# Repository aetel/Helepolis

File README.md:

Helepolis is an **educative** robot for those who want to have their **first contact** with robotics.

It's based around the Arduino platform, using an Arduino Nano as its brain.
It can be programmed to complete numerous tasks such as line following and sumo fighting.

---
### The machine includes:
* An Arduino Nano with ATMega 328p
* SHARP Distance Sensor
* 5 Reflective IR Sensors
* Differential Traction with 2 Pololu Micromotors
* Bluetooth module.
* 2 WS2812 RGB LED
* 4 5mm led
* I2C or SPI Expansion Module Port (intended use is for an ADXL345 3-axis accelerometer)
* Buzzer
* A few switches for general use

---
### In this repository you will find:
* EagleCAD project
<br>&nbsp;&nbsp;Includes the schematic and the PCB files
* TestCode
<br>&nbsp;&nbsp;A program to check all the sensors and actuators are working fine
* ExampleCode
<br>&nbsp;&nbsp;Line follower and sumo bot example program
* Assembly manuals
<br>&nbsp;&nbsp;Guided assembly manuals in English and Spanish
* BoM
<br>&nbsp;&nbsp;Bill of Materials used for the robot

---
### Android app:
You can download the app to control the robot at [Google Play](https://play.google.com/store/apps/details?id=aetel.helepolis), though you may be interested in building or modifying the code available in this repository.

---

Helepolis and its surrounding materials are published under [CC BY-SA 4.0](https://creativecommons.org/licenses/by-sa/4.0/)

Helepolis was designed by [Pablo dMM](https://github.com/PabloDMM "Pablo dMM") for Telecom Electronics Association [AETEL](http://aetel.io), based at the Campus Sur of [Universidad Politécnica de Madrid](http://upm.es).

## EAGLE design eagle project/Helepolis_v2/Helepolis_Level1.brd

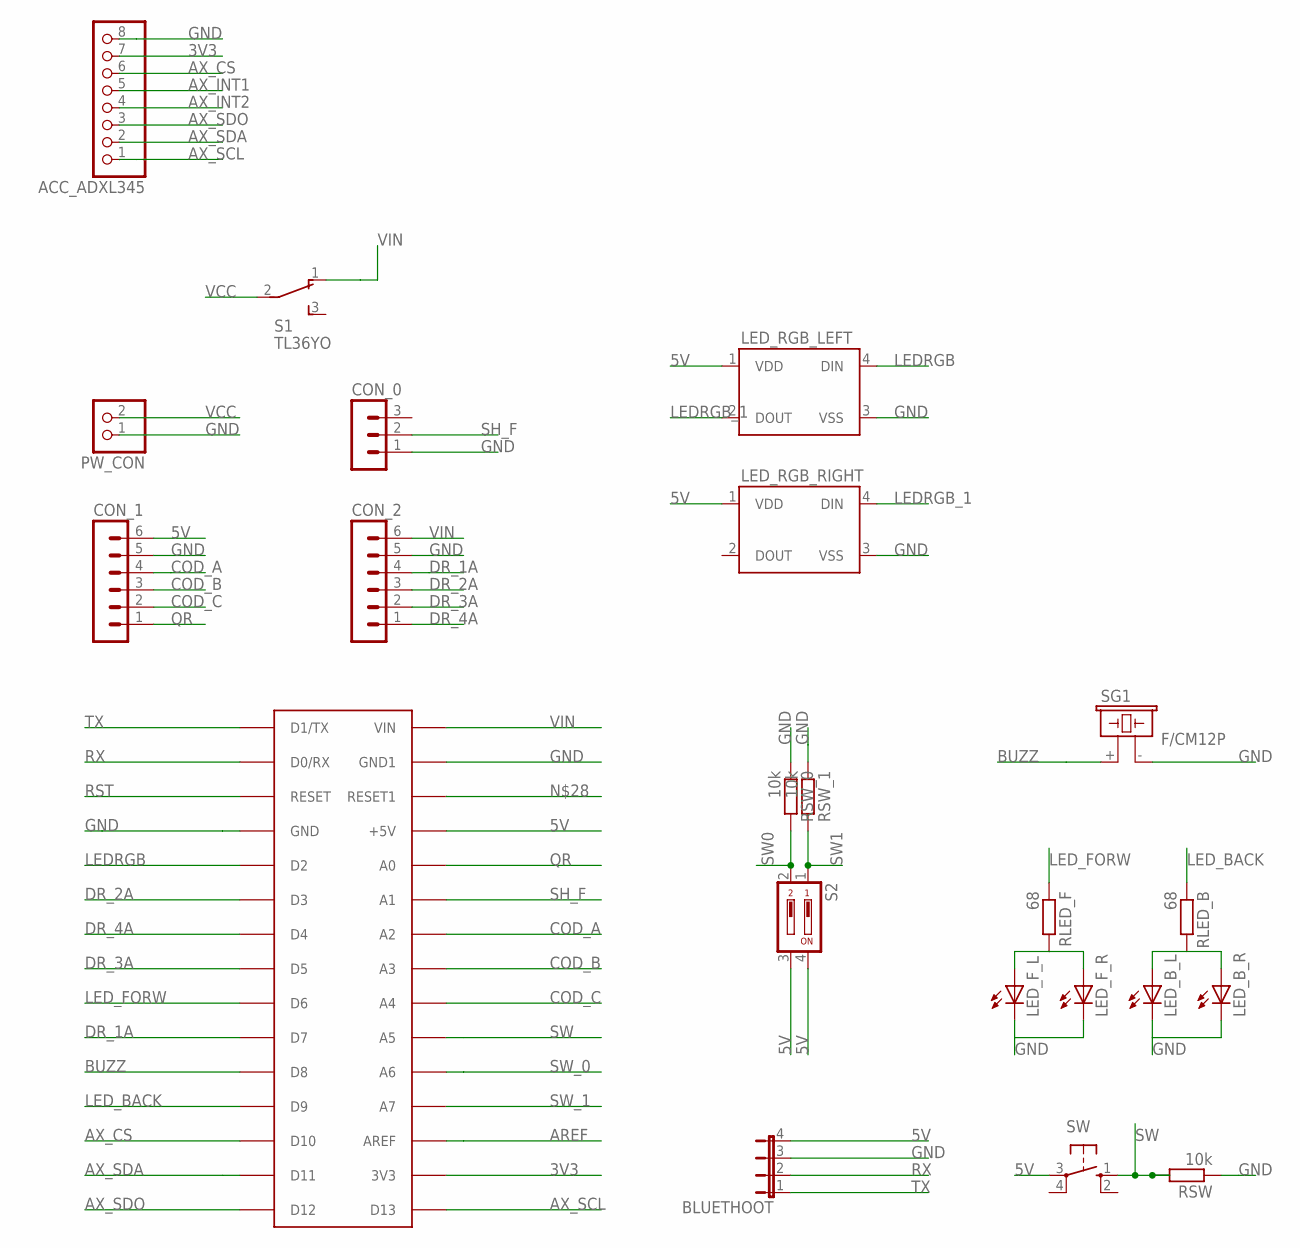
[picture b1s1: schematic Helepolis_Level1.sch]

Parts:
ACC_ADXL345: PINHD-1X8; 1X08
BLUETHOOT: JP4E; JP4
CON_0: MA03-1
CON_1, CON_2: MA06-1
LED_B_L: LED5MM
LED_B_R: LED5MM
LED_F_L: LED5MM
LED_F_R: LED5MM
LED_RGB_LEFT: WS2812B
LED_RGB_RIGHT: WS2812B
PW_CON: PINHD-1X2; 1X02
RLED_B: 68; R1206
RLED_F: 68; R1206
RSW: 10k; R1206
RSW_0, RSW_1: 10k; R1206
S1: TL36YO; TL3XYO
S2: DP02; DP-02
SG1: F/CM12P
SW: 10-XX; B3F-10XX
U$1: ARDUINONANO; PDIP-32

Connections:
3V3: ACC_ADXL345.7, U$1.3V3
5V: BLUETHOOT.4, CON_1.6, LED_RGB_LEFT.1 (VDD), LED_RGB_RIGHT.1 (VDD), S2.3, S2.4, SW.3, U$1.+5V
AREF: U$1.AREF
AX_CS: ACC_ADXL345.6, U$1.D10
AX_INT1: ACC_ADXL345.5
AX_INT2: ACC_ADXL345.4
AX_SCL: ACC_ADXL345.1, U$1.D13
AX_SDA: ACC_ADXL345.2, U$1.D11
AX_SDO: ACC_ADXL345.3, U$1.D12
BUZZ: SG1.+ (1), U$1.D8
COD_A: CON_1.4, U$1.A2
COD_B: CON_1.3, U$1.A3
COD_C: CON_1.2, U$1.A4
DR_1A: CON_2.4, U$1.D7
DR_2A: CON_2.3, U$1.D3
DR_3A: CON_2.2, U$1.D5
DR_4A: CON_2.1, U$1.D4
GND: ACC_ADXL345.8, BLUETHOOT.3, CON_0.1, CON_1.5, CON_2.5, LED_B_L.K (C), LED_B_R.K (C), LED_F_L.K (C), LED_F_R.K (C), LED_RGB_LEFT.3 (VSS), LED_RGB_RIGHT.3 (VSS), PW_CON.1, RSW.1, RSW_0.1, RSW_1.1, SG1.- (2), U$1.GND, U$1.GND1
LEDRGB: LED_RGB_LEFT.4 (DIN), U$1.D2
LEDRGB_1: LED_RGB_LEFT.2 (DOUT), LED_RGB_RIGHT.4 (DIN)
LED_BACK: RLED_B.1, U$1.D9
LED_FORW: RLED_F.1, U$1.D6
unnamed: LED_F_L.A, LED_F_R.A, RLED_F.2
unnamed: LED_B_L.A, LED_B_R.A, RLED_B.2
QR: CON_1.1, U$1.A0
RST: U$1.RESET
RX: BLUETHOOT.2, U$1.D0/RX
SH_F: CON_0.2, U$1.A1
SW: RSW.2, SW.1 (S), U$1.A5
SW0: RSW_0.2, S2.2
SW1: RSW_1.2, S2.1
SW_0: U$1.A6
SW_1: U$1.A7
TX: BLUETHOOT.1, U$1.D1/TX
VCC: PW_CON.2, S1.2
VIN: CON_2.6, S1.1 (O), U$1.VIN

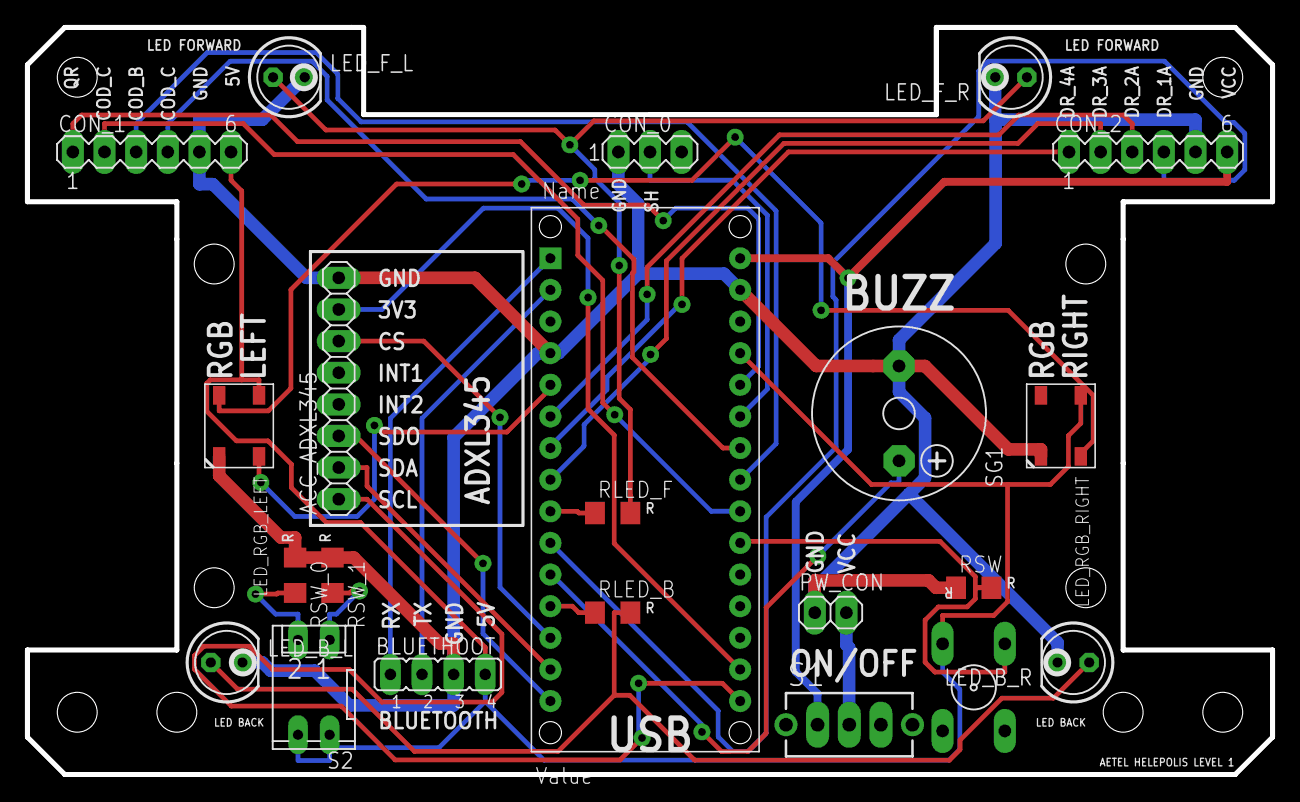
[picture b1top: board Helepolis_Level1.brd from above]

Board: 2 copper layers, 100.0 x 60.0 mm, 22 parts (0 on the bottom side), 30 nets.

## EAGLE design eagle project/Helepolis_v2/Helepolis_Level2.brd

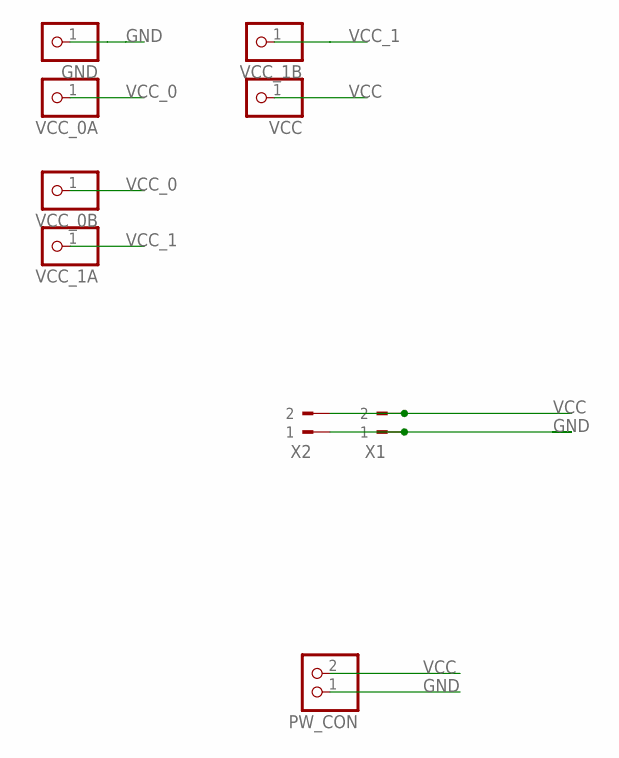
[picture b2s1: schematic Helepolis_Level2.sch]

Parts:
GND: PINHD-1X1; 1X01
PW_CON: PINHD-1X2; 1X02
VCC: PINHD-1X1; 1X01
VCC_0A, VCC_0B, VCC_1A, VCC_1B: PINHD-1X1; 1X01
X1, X2: 90-2

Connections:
GND: GND.1, PW_CON.1, X1.1, X2.1
VCC: PW_CON.2, VCC.1, X1.2, X2.2
VCC_0: VCC_0A.1, VCC_0B.1
VCC_1: VCC_1A.1, VCC_1B.1

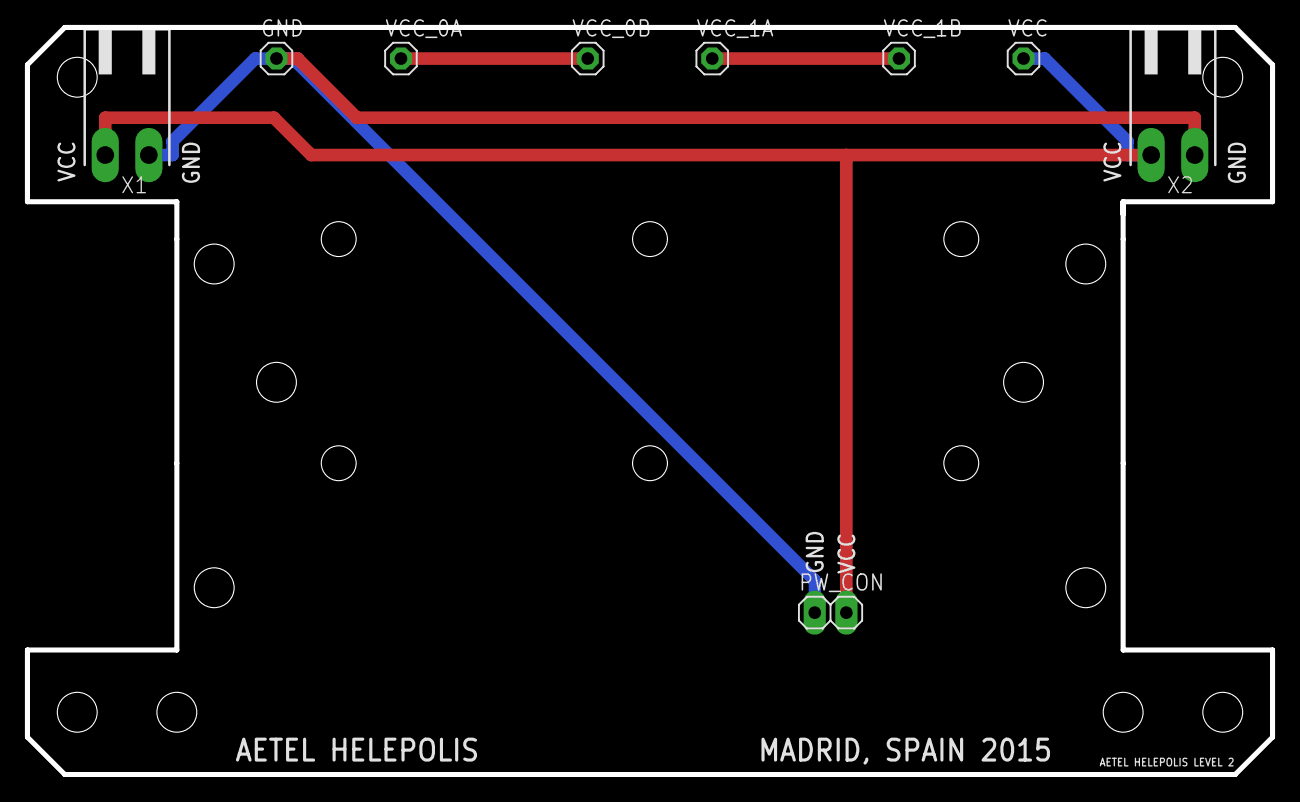
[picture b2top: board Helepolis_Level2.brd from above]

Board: 2 copper layers, 100.0 x 60.0 mm, 9 parts (0 on the bottom side), 4 nets.

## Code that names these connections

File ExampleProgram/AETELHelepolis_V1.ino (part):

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#define SW 16
#define SW_1 14
#define SW_0 15
#define BUZZ 8
#define LED_RGB 2
#define LED_FORW 6
#define LED_BACK 9
#define AX_CS 10
#define AX_SDA 11
#define AX_SDO 12
#define AX_SCL 13

const int borderThr = 900;
const int distanceThr = 300;
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
void setup(){
  Serial.begin(9600);
  pinMode(LED_FORW, OUTPUT);
  pinMode(LED_BACK, OUTPUT);
  pinMode(MUL_A, OUTPUT);
  pinMode(MUL_B, OUTPUT);
  pinMode(MUL_C, OUTPUT);
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
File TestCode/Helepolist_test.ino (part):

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#define SW 16
#define SW_1 14
#define SW_0 15
#define COD_A 19
#define COD_B 18
#define COD_C 17
#define BUZZ 8
#define LED_FORW 6
#define LED_BACK 9
#define NUMPIXELS 2

//Creates an object to control RGB leds
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
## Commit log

2016-03-17 Primer commit
2016-03-17 Added first version README.md
2016-03-17 Extended README.md
    Added functions and repo directories
2016-03-17 README.md fixes and image
2016-03-17 Fixed image
2016-03-17 Even moar fixes
    I should *really* learn Markdown
2016-03-17 I suck at MD
    Had to use old plain HTML :(
2016-03-17 Test program to check every part of the robot
    Adafruit Neopixel library is necessary to compile.
2016-03-17 Added guides, Android code and eagle project
2016-03-28 Added files via upload
    Basic program covering the functionalities of:
    - Line Follower Robot
    - Sumobot (Black border)
    - Sumobot (White border)
    The use of the Bluetooth Android App control implemented by Javier Arrieta will be soon included in the same program.
2016-03-28 Moved some files into folders
    …also added CC badge to readme.md
2016-04-21 Solved problems with Bluetooth mode
2016-10-12 Fixed problems with Distance test and Motor test. Added comments and clean code for understand program in the future

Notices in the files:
TestCode/Helepolist_test.ino:
Copyright 2016 AETEL
The AETEL Helepolis is released under an Attributtion-ShareAlike 4.0 International (CC BY-SA 4.0) . Therefore, anyone is free to:
•  Share – Copy and redistribute the material in any medium or format.
parts and their libraries:
SparkFun-LED_copia: Licensing: Creative Commons ShareAlike 4.0 International - https://creativecommons.org/licenses/by-sa/4.0
